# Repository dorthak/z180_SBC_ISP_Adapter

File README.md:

# z180_SBC_ISP_Adapter

Adapter board between s100computers' z180 SBC board and the z80-Retro! in-system programmer

This adapter is designed to be placed between the ROM socket of the s100Computers z180 SBC board (https://s100computers.com/My%20System%20Pages/Z180%20SBC/Z180%20SBC1.htm) and the z80-Retro! in-system programmer (https://github.com/Z80-Retro/2065-Z80-programmer) to allow in-system programming of a ROM.

Note that the programmer only suports a 16 bit (64k) address, whereas the ROM on the z180 board supports a 19 bit address (512k).  Accordingly, only the bottom 64k of the ROM chip can be programmed this way.

**J1** should be populated with long header pins below the board (or stacked machined IC sockets work well) that will be inserted into the U3 socket on the z180 SBC board.

**U1** is a 32-pin ZIFF socket, into which the SST39SF040 ROM chip will be placed.

**J2** is a standard 2x20 header, placed above the board, to which the in-system programmer can be attache directly, or with a ribbon cable or dupont leads.

(Note that this is V1.0 of the board, with an incorrect pinout on J2.  Dupont leads are being used to correctly connect the ISP to J2.)

**R1-R3** are pull-down resistors for A16-A18 address lines which cannot be accessed by the programmer.  However, in practice, I have found that they need not be populated.

**J3** can be equipped with header pins or sockets, above or below the board, straight or right angle, as best fits mechanically.  This header pulls out several signals from the programmer that aren't present in the ROM socket.  Only two of these are important - RESET* and BUSREQ*.  The other three signals aren't currently needed but have been placed there for completeness and future-proofing.

The two necessary signals need to be connected to the z180 board using jumper wires and micrograbbers, or similair.  On v0.9 of the z180 SBC, the best place I found to connect these are as follows:  

RESET* to U30, pin 4.  

BUSREQ* to R20 on the "right" leg (the one closer to the interior of the board, away from the edge).  

Note that R20 isn't present on earlier reviisions of the z180 SBC, and therefore a different location must be found for connecting this signal.  Perhaps pin 8 of U21.

Version 1.0 has incorrect pinout for connecting to the programmer, but can be made to work with dupont wires.  Also missing some pullup resistors, HOWEVER, the adapter seems to work fine WITHOUT the resistors installed.

Version 1.1 has fixed the pinout and additional pullup resistor pads, and changed mechanical layout to better fit, but it has not been tested.

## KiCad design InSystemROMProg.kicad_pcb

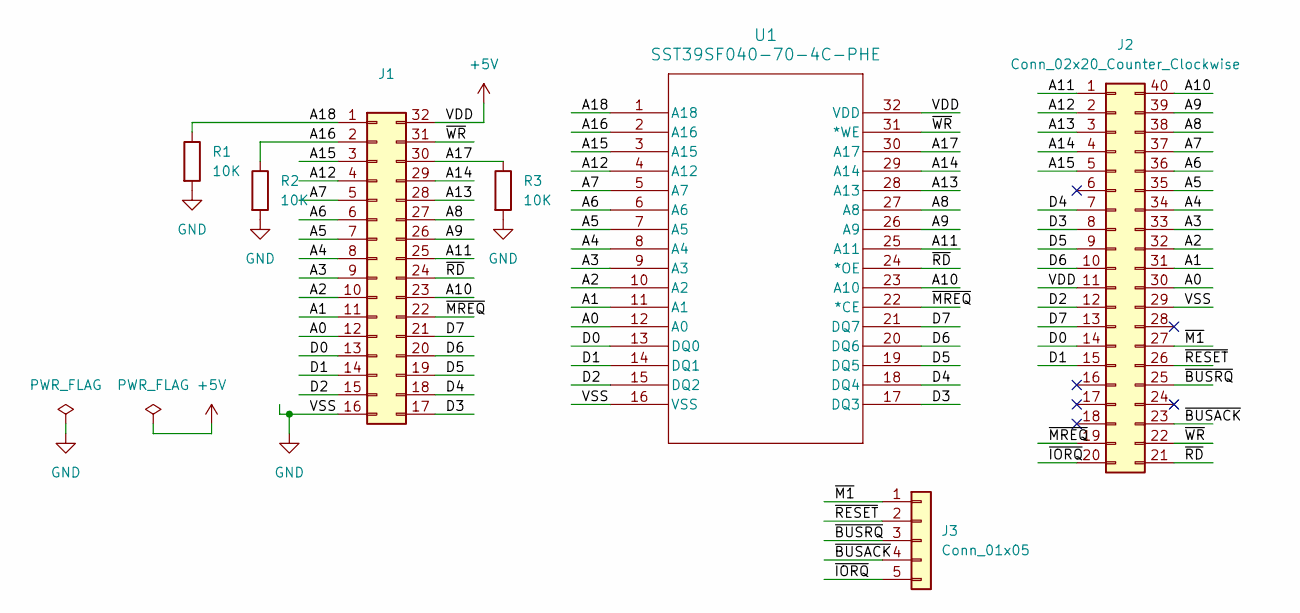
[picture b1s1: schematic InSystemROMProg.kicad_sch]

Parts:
J1: Conn_02x14_Counter_Clockwise; DIP-32_W15.24mm_Socket_LongPads
J2: Conn_02x20_Counter_Clockwise; PinHeader_2x20_P2.54mm_Vertical
J3: Conn_01x05; PinHeader_1x05_P2.54mm_Vertical
R1, R2, R3: 10K; R_Axial_DIN0207_L6.3mm_D2.5mm_P7.62mm_Horizontal
U1: SST39SF040-70-4C-PHE; ZIFF Socket - DIP-32 - 15.24mm x 2.54mm

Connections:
+5V: J1.32, J2.11, U1.32 (VDD)
/A0: J1.12, J2.30, U1.12 (A0)
/A1: J1.11, J2.31, U1.11 (A1)
/A2: J1.10, J2.32, U1.10 (A2)
/A3: J1.9, J2.33, U1.9 (A3)
/A4: J1.8, J2.34, U1.8 (A4)
/A5: J1.7, J2.35, U1.7 (A5)
/A6: J1.6, J2.36, U1.6 (A6)
/A7: J1.5, J2.37, U1.5 (A7)
/A8: J1.27, J2.38, U1.27 (A8)
/A9: J1.26, J2.39, U1.26 (A9)
/A10: J1.23, J2.40, U1.23 (A10)
/A11: J1.25, J2.1, U1.25 (A11)
/A12: J1.4, J2.2, U1.4 (A12)
/A13: J1.28, J2.3, U1.28 (A13)
/A14: J1.29, J2.4, U1.29 (A14)
/A15: J1.3, J2.5, U1.3 (A15)
/A16: J1.2, R2.1, U1.2 (A16)
/A17: J1.30, R3.1, U1.30 (A17)
/A18: J1.1, R1.1, U1.1 (A18)
/D0: J1.13, J2.14, U1.13 (DQ0)
/D1: J1.14, J2.15, U1.14 (DQ1)
/D2: J1.15, J2.12, U1.15 (DQ2)
/D3: J1.17, J2.8, U1.17 (DQ3)
/D4: J1.18, J2.7, U1.18 (DQ4)
/D5: J1.19, J2.9, U1.19 (DQ5)
/D6: J1.20, J2.10, U1.20 (DQ6)
/D7: J1.21, J2.13, U1.21 (DQ7)
/~BUSACK: J2.23, J3.4
/~BUSRQ: J2.25, J3.3
/~IORQ: J2.20, J3.5
/~M1: J2.27, J3.1
/~MREQ: J1.22, J2.19, U1.22 (*CE)
/~RD: J1.24, J2.21, U1.24 (*OE)
/~RESET: J2.26, J3.2
/~WR: J1.31, J2.22, U1.31 (*WE)
GND: J1.16, J2.29, R1.2, R2.2, R3.2, U1.16 (VSS)

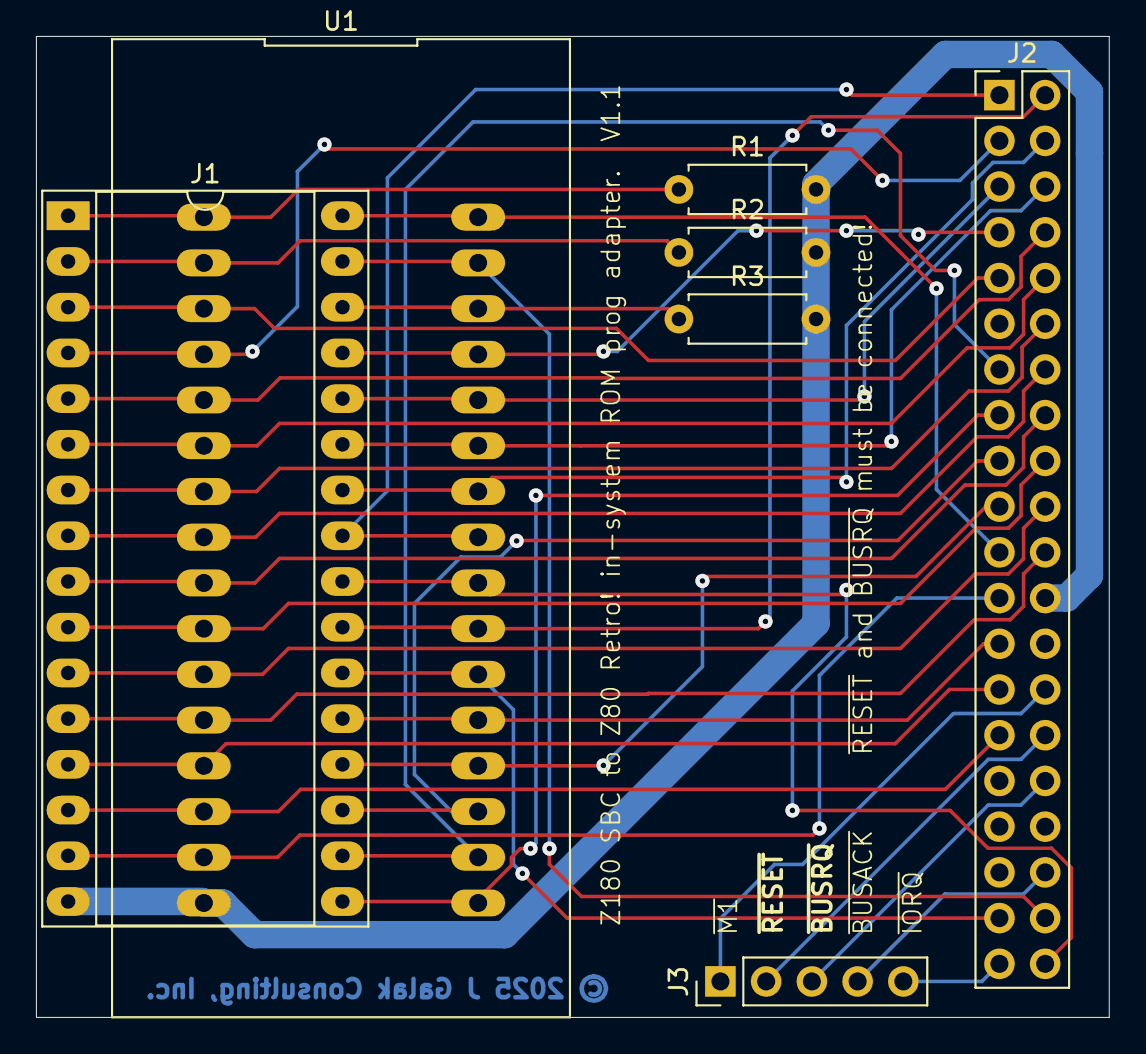
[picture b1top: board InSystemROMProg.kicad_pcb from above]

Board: 2 copper layers, 59.6 x 54.5 mm, 7 parts (0 on the bottom side), 37 nets.

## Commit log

2026-03-02 Version 1.1 - pinout and pullups fixed, but untested
2026-03-02 Edited readme
2026-03-02 edited read.me
2026-03-17 Added Images
2026-03-17 Working on readme file

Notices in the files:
InSystemROMProg.kicad_pcb:
© 2025 J Galak Consulting, Inc.
